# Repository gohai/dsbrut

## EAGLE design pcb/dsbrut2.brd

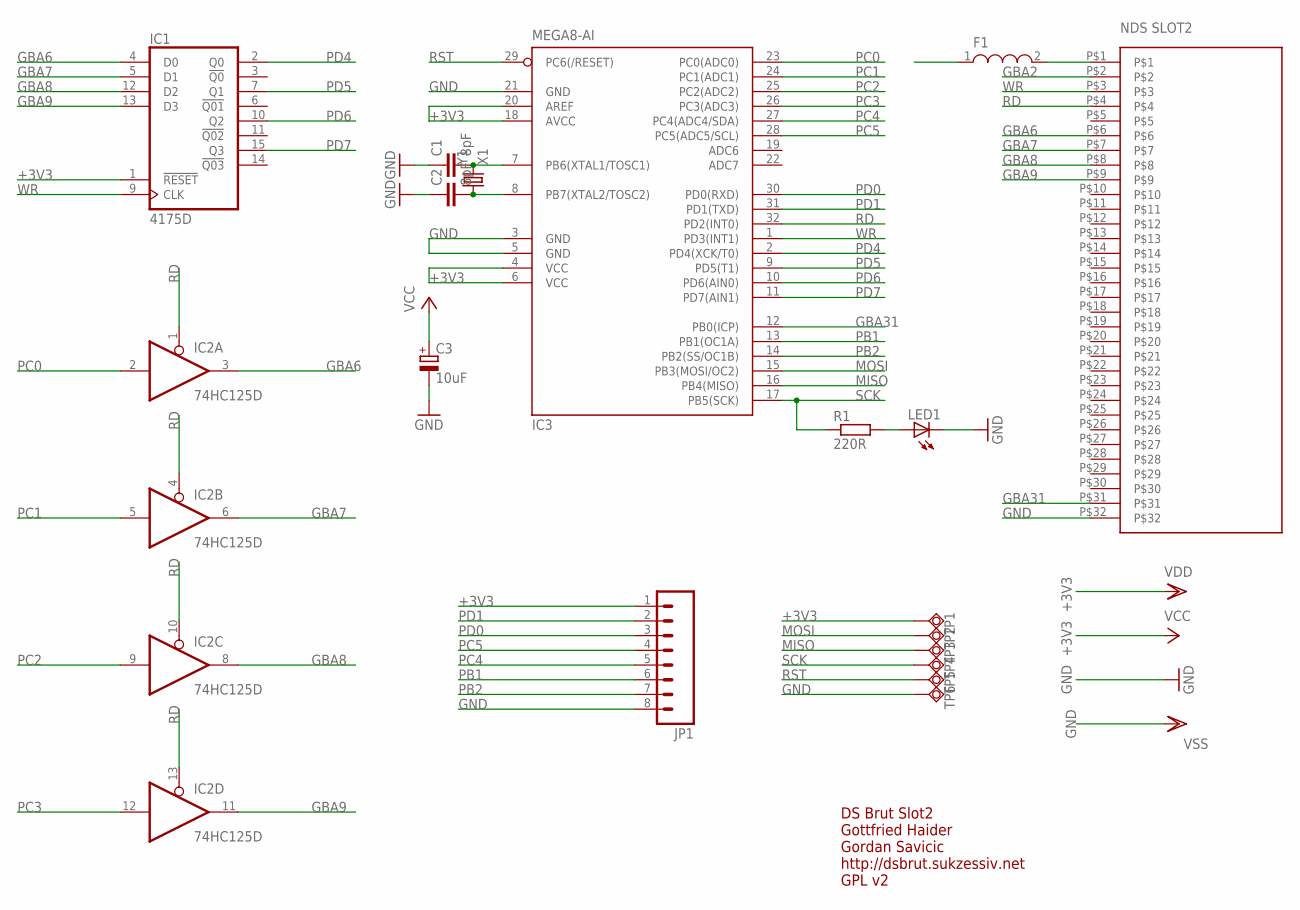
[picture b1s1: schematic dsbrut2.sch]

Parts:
C1, C2: 8pF; C0603K
C3: 10uF; SMC_A
F1: F1; L1812
IC1: 4175D; SO16
IC2: 74HC125D; SO14
IC3: MEGA8-AI; TQFP32-08
JP1: M08LONGPADS; 1X08_LONGPADS
LED1: LED0603; LED-0603
R1: 220R; M0805
TP1, TP2, TP4, TP5, TP6: TPSQTP16R; TP16R
TP3: TPSQTP16SQ; TP16SQ
U$1: DS_CARTRIDGE_SLOT2; DS-CARTRIDGE-SLOT2
Y1: X1; CRYSTAL-SMD-5X3

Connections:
+3V3: C3.+, F1.1, IC1.1 (!RESET), IC1.16 (VDD), IC2.14 (VCC), IC3.4 (VCC), IC3.6 (VCC), IC3.18 (AVCC), IC3.20 (AREF), JP1.1, TP1.TP
GBA2: U$1.P$2
GBA6: IC1.4 (D0), IC2.3 (O), U$1.P$6
GBA7: IC1.5 (D1), IC2.6 (O), U$1.P$7
GBA8: IC1.12 (D2), IC2.8 (O), U$1.P$8
GBA9: IC1.13 (D3), IC2.11 (O), U$1.P$9
GBA31: IC3.12 (PB0(ICP)), U$1.P$31
GND: C1.1, C2.1, C3.-, IC1.8 (VSS), IC2.7 (GND), IC3.3 (GND), IC3.5 (GND), IC3.21 (GND), JP1.8, LED1.C, TP6.TP, U$1.P$32
MISO: IC3.16 (PB4(MISO)), TP3.TP
MOSI: IC3.15 (PB3(MOSI/OC2)), TP2.TP
unnamed: F1.2, U$1.P$1
unnamed: C1.2, IC3.7 (PB6(XTAL1/TOSC1)), Y1.3 (2)
unnamed: LED1.A, R1.2
PB1: IC3.13 (PB1(OC1A)), JP1.6
PB2: IC3.14 (PB2(SS/OC1B)), JP1.7
PB7: C2.2, IC3.8 (PB7(XTAL2/TOSC2)), Y1.1
PC0: IC2.2 (I), IC3.23 (PC0(ADC0))
PC1: IC2.5 (I), IC3.24 (PC1(ADC1))
PC2: IC2.9 (I), IC3.25 (PC2(ADC2))
PC3: IC2.12 (I), IC3.26 (PC3(ADC3))
PC4: IC3.27 (PC4(ADC4/SDA)), JP1.5
PC5: IC3.28 (PC5(ADC5/SCL)), JP1.4
PD0: IC3.30 (PD0(RXD)), JP1.3
PD1: IC3.31 (PD1(TXD)), JP1.2
PD4: IC1.2 (Q0), IC3.2 (PD4(XCK/T0))
PD5: IC1.7 (Q1), IC3.9 (PD5(T1))
PD6: IC1.10 (Q2), IC3.10 (PD6(AIN0))
PD7: IC1.15 (Q3), IC3.11 (PD7(AIN1))
RD: IC2.1 (OE), IC2.4 (OE), IC2.10 (OE), IC2.13 (OE), IC3.32 (PD2(INT0)), U$1.P$4
RST: IC3.29 (PC6(/RESET)), TP5.TP
SCK: IC3.17 (PB5(SCK)), R1.1, TP4.TP
WR: IC1.9 (CLK), IC3.1 (PD3(INT1)), U$1.P$3

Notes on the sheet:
DS Brut Slot2 Gottfried Haider Gordan Savicic http://dsbrut.sukzessiv.net GPL v2

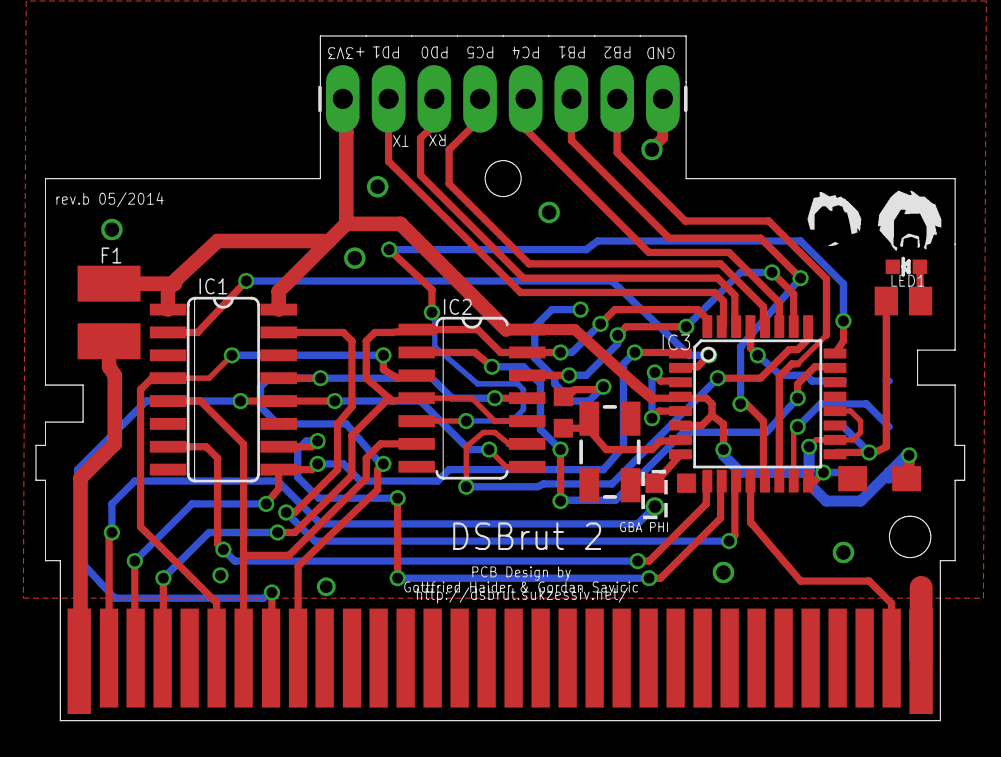
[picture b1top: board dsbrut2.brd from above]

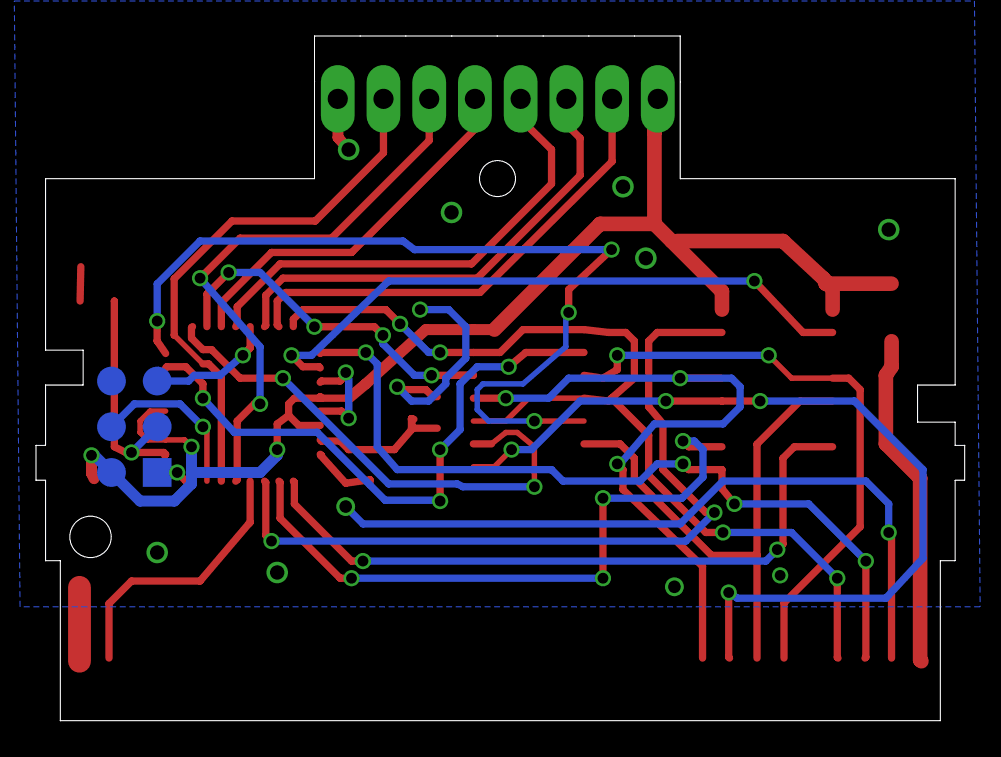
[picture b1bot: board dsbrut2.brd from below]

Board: 2 copper layers, 51.6 x 38.0 mm, 18 parts (6 on the bottom side), 31 nets.

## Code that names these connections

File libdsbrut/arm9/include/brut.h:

#ifndef _BRUT_H_
#define _BRUT_H_


// available pins, left to right
#define PC5			19
#define PC4			18
#define PD3			3
#define PD4			4
#define PD6			6
#define PD5			5
#define PC3			17				// only exposed on ds brut uart only

// for the adxl330 3-axis accelerometer
#define ACCEL_X			1
#define ACCEL_Y			2
#define ACCEL_Z			3

// to helo you arduino people
#define HIGH			true
#define LOW			false


/**
 *	read the value of an analog pin.
 *
 *	works with PC5, PC4; PC3 (ds brut uart only)
 *	you can use this function to read from a build-in adxl330 
 *	accelerometer, using ACCEL_{X,Y,Z} as pin.
 *	@param pin		pin to use (see pin definitions above)
 *	@return			value (0-1023)
 */
uint16 analog_read(uint8 pin);


/**
 *	start a fast adc conversion of an analog pin.
 *
 *	this function continuously returns the value of the analog pin as an 
 *	uint8 (8 bit) in the normal input queue (so read with uart_read(), 
 *	etc). until this function is called again with start set to false, 
 *	all other data send to the device will be ignored.
 *	@param start		true to start, false to stop
 *	@param pin		pin to use (see pin definitions above)
 */
void analog_read_fast(bool start, uint8 pin);

 
/**
 *	write a pwm value to a pin.
 *
 *	works with PD3, PD6, PD5
 *	@param pin		pin to use (see pin definitions above)
 *	@param val		value
 */
void analog_write(uint8 pin, uint8 val);


/**
 *	reset the device.
 *
 *	this function triggers a watchdog reset on the atmega micro-
 *	controller. a modified bootloader is necessary for this to work, 
 *	otherwise no reset will be performed.
 *	@param wait		wait for the card to become available again
 */
void atmega_reset(bool wait);


/**
 *	read registers on the device.
 *
 *	see atmega168 datasheet, p. 343f.
 *	@param reg		register address
 *	@return			register value
 */
uint8 atmega_read_8(uint8 reg);


/**
 *	write to registers on the device.
 *
 *	see atmega168 datasheet, p. 343f.
 *	@param reg		register address
 *	@param val		value to set
 */
void atmega_write_8(uint8 reg, uint8 val);


/**
 *	read the value of a pin.
 *
 *	@param pin		pin to use (see pin definitions above)
 *	@return			HIGH or LOW
 */
bool digital_read(uint8 pin);


/**
 *	set a pin either high or low.
 *
 *	@param pin		pin to use (see pin definitions above)
 *	@param val		HIGH or LOW
 */
void digital_write(uint8 pin, bool val);


/**
 *	receive data over the i2c bus.
 *
 *	use PC4 as SDA and PC5 as SCL line.
 *	the device joins the i2c bus as master. addr has the destination 
 *	address in the lower 7 bits. internally, they are being left-shifted 
 *	and the read/write bit appended (like on arduino).
 *	@param addr		source address (slave)
 *	@param dest		destination buffer
 *	@param size		size of destination buffer in bytes
 *	@return			number of bytes received
 */
uint8 i2c_receive(uint8 addr, uint8 *dest, uint8 size);


/**
 *	send data over the i2c bus.
 *
 *	use PC4 as SDA and PC5 as SCL line.
 *	the device joins the i2c bus as master. addr has the destination 
 *	address in the lower 7 bits. internally, they are being left-shifted 
 *	and the read/write bit appended (like on arduino).
 *	@param addr		destination address (slave)
 *	@param src		data to send
 *	@param size		number of bytes to send
 *	@retval 0		success
 *	@retval 1		size to big for (atmega) buffer
 *	@retval 2		address send, nack received
 *	@retval 3		data send, nack received
 *	@retval 4		other i2c error (lost bus arbitration, bus error)
 *	@retval 255		out of memory
 */
uint8 i2c_send(uint8 addr, const uint8 *src, uint8 size);


/**
 *	send an EM4102 sequence
 *
 *	data is expected to be five bytes. first byte holds the manufacturer 
 *	id while the other ones hold the unique (card) id.
 *	needs firmware version 0x13 or higher.
 *	@param pin		pin to use (see pin definitions above)
 *	@param data		data buffer (expected to be five bytes)
 *	@param tries	number of consecutive times to send the sequence
 *	@return			true if successful, false if not
 */
bool em4102_send(uint8 pin, const uint8* data, uint8 tries);


#endif	// _BRUT_H_

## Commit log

2008-10-09 initial import
2008-10-09 remove libdsuart-0.1 distribution file
2008-10-20 libdsuart-0.2 + added uartI2CSend(), uartI2CReceive() + Card Line interrupt functionality
2008-10-20 remove build directories
2008-11-16 changed uartOpen() to wait for cartridge to become accessible (prevents bogus readings right after bootup) changed variable type to the more common {u,}int{8,16,32} fixed a bug in main.c that ate eve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
2009-01-06 temporary remove libDSUart folder (for rename) add bootloader
2009-01-06 commit latest testing version of libDSuart
2009-01-06 add some files I missed fixup ignores
2009-01-25 initial libdsbrut commit
2009-01-25 remove build directory
2009-02-04 more work on libdsbrut
2009-03-26 import libdsbrut 0.9 (complete rewrite)
2009-03-26 change ignore lists
2009-03-27 add plan
2009-03-27 we like unix line endings :)
2009-03-30 add more ideas
2009-04-05 started implementing bill's fast adc code
2009-04-06 made a function for bill's fast adc code (untested, still) more changes to the firmware made uart_read() handle dummy reads (dest is NULL)
2009-04-08 add more fast adc related documentation
2009-04-20 more plan updates
2009-08-20 fix analog_read(), analog_read_fast() on custom pins (makes reading the 3g sensor work) cleanup atmega sketch a bit copy new libdsbrut revision to projects compile sources using latest devkitPro (lib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
2009-08-20 update documentation
2009-09-08 add ds bluetooth code add some bluetooth testing code to term fixed uart_readln() fixed uart_requeue() updated term_scsd binary (for supercard sd lite) changed tab width (to 8 characters) minor docum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
2009-09-13 add bt_connect(), bt_disconnect() add testing code to term
2009-09-13 fixes to bt_disconnect()
2009-09-18 add a function for setting the parity on the uart device add a function for block-like writing the content of a buffer over the uart device update firmware sketch
2009-09-24 GS edited bluetooth howto
2009-10-04 make libdsbrut also work on arm7 this needs a time7.h as time() seems to be broken on arm7 make uart_write_block() not allocate memory on the fly update project binaries
2009-10-11 update firmware for release compile binaries against latest devkitPro version update documentation
2009-10-20 compile the static bootloader with the improved HardwareSerial library
2010-04-11 add em4102 test code (needs latest firmware) fix compile warning
2010-04-14 fix a typo in em4102 checksum generation add documentation
2010-05-07 add support for controlling up to 4 servos rebuild everything with latest devkitpro and arduino 0018
2010-05-07 update plan
2011-06-11 Convert svn:ignore properties to .gitignore
2014-05-17 Start Slot-2 development
2014-05-21 schematic/board first draft
2014-05-21 updated isp progheader - please verify orientation
2014-05-22 added rst, sck led, aref vcc, cleanup
2014-05-23 Add GBA{8,9} and connections between IC{1,2} and the AtMega
2014-05-23 Add a variant with only a two bit data bus for discussion
2014-05-26 from 2to4to2 layers - added gba4/5/6/7/8 etc...
2014-05-27 Connected RD to ATmega, added TX/RX labels, removed ground plane underneath Slot -2 pins
2014-05-27 added fuse, fixed ic1 power supply with VSS
2014-05-27 Changed fuse label, moved a via, minor trace beautification
2014-05-27 power supply pin 16 on ic1
2014-05-27 Made pin1 of the ICSP connector square
2014-05-28 added crystal, jumper bridge for gba2
2014-05-28 cleanup, added our two faces on silkscreen layer
2014-05-28 added c3 between vcc and gnd, moved c2 away from steg
2014-05-29 Renamed GBA PHI, added label to F1, moved GBA PHI solder bridge slightly, moved some labels slightly
2014-05-29 solder bridge drc
2014-05-29 Label Xtal caps as 18uF, moving a few labels
2014-05-29 Changed 18pF to 8pF, labeled C3 as 10uF
2014-05-29 changed soldermask of gba2 bridge, added gerber files, added CAM file for dsbrut2, zip file for order in sexy bash script
2014-06-01 Cleanup
2014-06-01 Add gerber files for rev. a
2014-06-01 Added prelim. bill of materials for rev. a
2014-06-01 Update Eagle library with latest from Gordo
2014-06-26 Switch from ATMega 328 to 328P
2014-06-26 Add stencil for rev a
2014-06-26 Swap ICSP pads on the bottom, add some keepouts
2014-07-13 Update BOM
2014-07-13 Add documentation on how to program the DS Brut 2
2015-03-07 Make firmware compile with recent versions of Arduino
2015-03-07 Update programming guide
2015-12-30 Port libspi to current devKitPro
2015-12-30 Fix printf warnings

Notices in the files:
parts and their libraries:
SparkFun-Connectors: Licensing: Creative Commons ShareAlike 4.0 International - https://creativecommons.org/licenses/by-sa/4.0
